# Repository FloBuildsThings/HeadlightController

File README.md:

# HeadlightController
Prototype for controlling a Headlight

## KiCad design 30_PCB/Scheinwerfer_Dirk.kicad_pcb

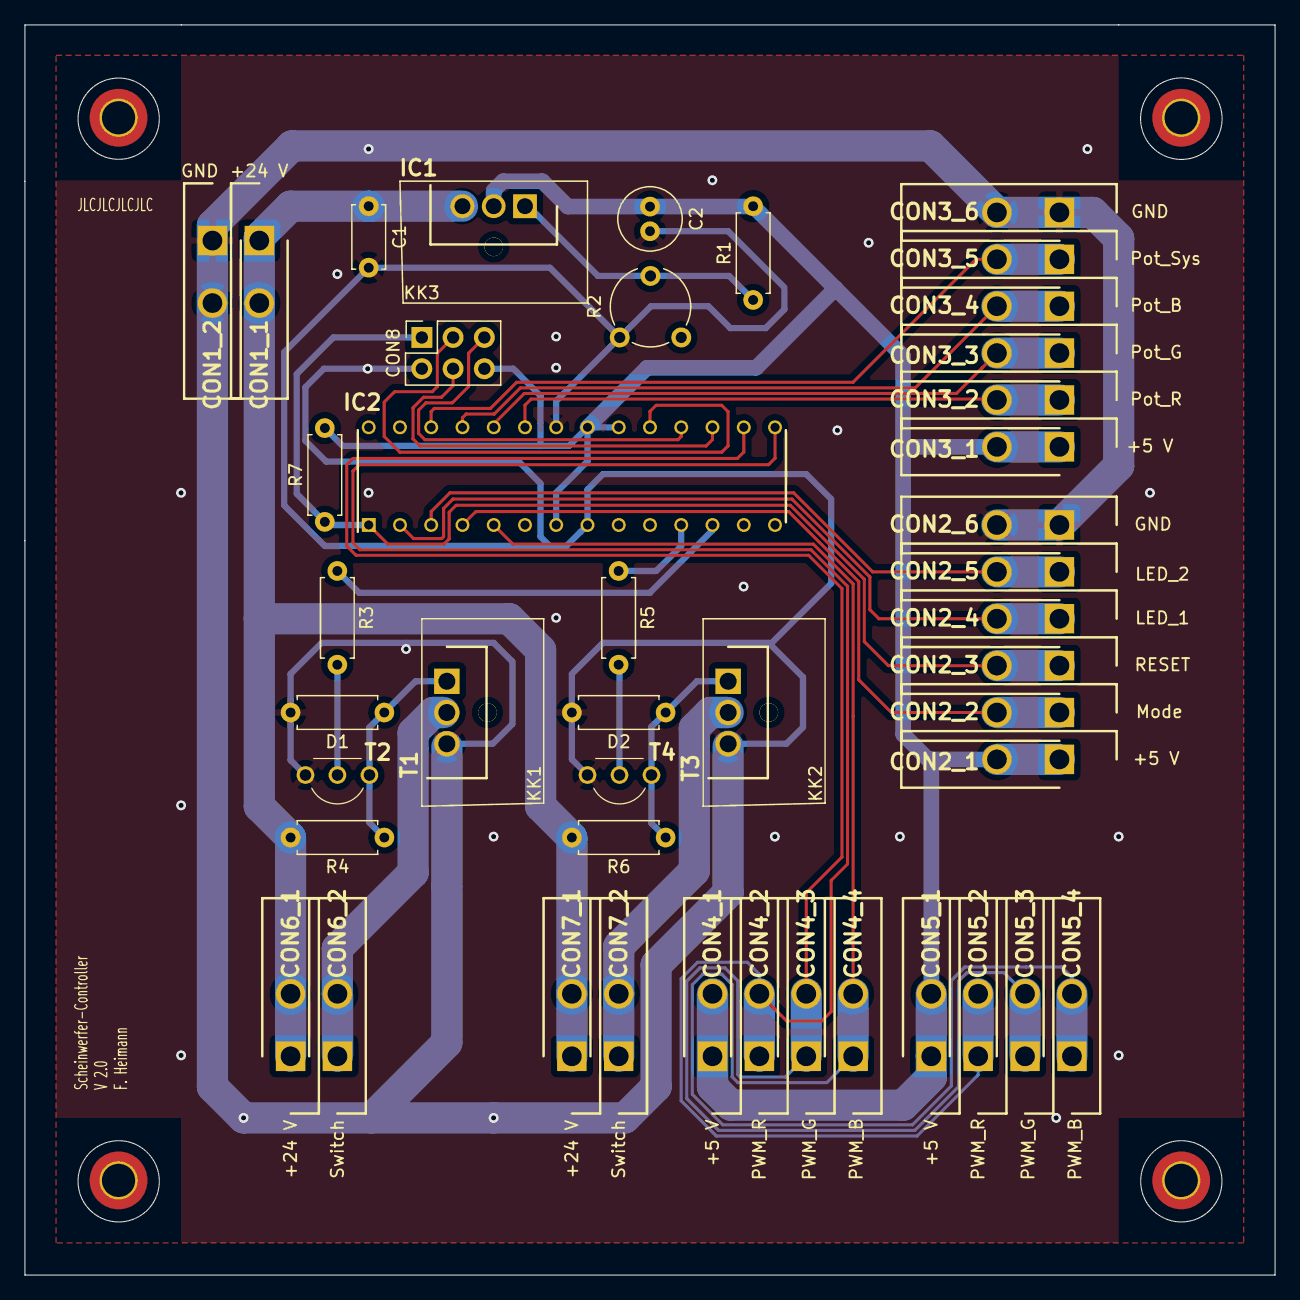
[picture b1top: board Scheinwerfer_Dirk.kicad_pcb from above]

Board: 2 copper layers, 101.6 x 101.6 mm, 47 parts (0 on the bottom side), 26 nets.

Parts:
C1: 0,1u; C_Disc_D5.0mm_W2.5mm_P5.00mm
C2: 1u; C_Radial_D5.0mm_H11.0mm_P2.00mm
CON1_1, CON1_2, CON2_1, CON2_2, CON2_3, CON2_4, CON2_5, CON2_6, CON3_1, CON3_2, CON3_3, CON3_4, CON3_5, CON3_6, CON4_1, CON4_2, CON4_3, CON4_4, CON5_1, CON5_2, CON5_3, CON5_4, CON6_1, CON6_2, CON7_1, CON7_2: 1704994; SHDR2W100P508X381_2X1_460X1750X1420P
CON8: ISP_DW_Connector
D1, D2: D_Zener; R_Axial_DIN0207_L6.3mm_D2.5mm_P7.62mm_Horizontal
IC1: LM317BTG; TO254P482X997X2018-3P
IC2: ATMEGA328P-PU; DIP794W53P254L3467H457Q28N
KK1, KK2, KK3: SK95-2M3; Heatsink_TO-220_L10_B15_H19.75
R1: 240; R_Axial_DIN0207_L6.3mm_D2.5mm_P7.62mm_Horizontal
R2: 3306F-1-504; Potentiometer_Piher_PT-6-V_Vertical
R3, R5: 120; R_Axial_DIN0207_L6.3mm_D2.5mm_P7.62mm_Horizontal
R4, R6: 10k; R_Axial_DIN0207_L6.3mm_D2.5mm_P7.62mm_Horizontal
R7: 4,7k; R_Axial_DIN0207_L6.3mm_D2.5mm_P7.62mm_Horizontal
T1, T3: IRFZ44N; TO254P483X1016X2223-3P
T2, T4: BC547ATA; TO-92__TO-226_

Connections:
+5V: C2.1, CON2_1.1, CON2_1.2, CON3_1.1, CON3_1.2, CON4_1.1, CON4_1.2, CON5_1.1, CON5_1.2, CON8.4, IC1.2, IC2.7, IC2.20, IC2.21, R1.2, R7.2
+24V: C1.1, CON1_1.1, CON1_1.2, CON6_1.1, CON6_1.2, CON7_1.1, CON7_1.2, IC1.3, R4.2, R6.2
/LED_1: CON2_4.1, CON2_4.2, IC2.2
/LED_2: CON2_5.1, CON2_5.2, IC2.3
/PWM_1: IC2.12, R3.1
/PWM_2: IC2.11, R5.1
/PWM_B: CON4_4.1, CON4_4.2, CON5_4.1, CON5_4.2, IC2.5
/PWM_G: CON4_3.1, CON4_3.2, CON5_3.1, CON5_3.2, IC2.16
/PWM_R: CON4_2.1, CON4_2.2, CON5_2.1, CON5_2.2, IC2.15
/Pot_B: CON3_4.1, CON3_4.2, IC2.25
/Pot_G: CON3_3.1, CON3_3.2, IC2.24
/Pot_R: CON3_2.1, CON3_2.2, IC2.23
/Pot_Sys: CON3_5.1, CON3_5.2, IC2.26
/SW_Mode: CON2_2.1, CON2_2.2, IC2.4
/uC_MISO: CON8.3, IC2.18
/uC_MOSI: CON8.5, IC2.17
/uC_RESET: CON2_3.1, CON2_3.2, CON8.1, IC2.1, R7.1
/uC_SCK: CON8.2, IC2.19
GND: C1.2, C2.2, CON1_2.1, CON1_2.2, CON2_6.1, CON2_6.2, CON3_6.1, CON3_6.2, CON8.6, D1.2, D2.2, IC2.8, IC2.22, R2.3, T1.3, T2.3, T3.3, T4.3
unnamed: CON6_2.1, CON6_2.2, T1.2
unnamed: CON7_2.1, CON7_2.2, T3.2
unnamed: D1.1, R4.1, T1.1, T2.1
unnamed: D2.1, R6.1, T3.1, T4.1
unnamed: IC1.1, R1.1, R2.2
unnamed: R3.2, T2.2
unnamed: R5.2, T4.2

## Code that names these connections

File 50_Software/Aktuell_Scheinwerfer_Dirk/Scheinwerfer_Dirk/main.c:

/*
 * Scheinwerfer_Dirk.c
 *
 * Created: 03.07.2020 08:35:33
 * Author : flo97
 */ 

/*
	Controller : ATMEGA328P U
	
	Pinout:
									   V
	ISP5	PCINT14/RESET		PC6	 1	28 PC5	ADC5/SCL/PCINT13	
	LED_1	PCINT16/RXD			PD0	 2	27 PC4	ADC4/SDA/PCINT12	
	LED_2	PCINT17/TXD			PD1	 3	26 PC3	ADC3/PCINT11		Poti Sys
	SW_MODE	PCINT18/INT0		PD2  4	25 PC2	ADC2/PCINT10		Poti B
	PWM B	PCINT19/OC2B/INT1	PD3  5	24 PC1	ADC1/PCINT9			Poti G
			PCINT20/XCK/T0		PD4  6	23 PC0	ADC0/PCINT8			Poti R
	5V							VCC  7	22 GND						0V
	0V							GND  8	21 AREF						5V
			PCINT6/XTAL1/TOSC1	PB6	 9	20 AVCC						5V
			PCINT7/XTAL2/TOSC2	PB7 10	19 PB5	SCK/PCINT5			ISP0
	FET1.2	PCINT21/OC0B/T1		PD5 11	18 PB4	MISO/PCINT4			ISP2
	FET1.1	PCINT22/OC0A/AIN0	PD6 12	17 PB3	MOSI/OC2A/PCINT3	ISP8
			PCINT23/AIN1		PC7 13	16 PB2	SS/OC1B/PCINT2		PWM G
			PCINT0/CLKO/ICP1	PB0 14	15 PB1	OC1A/PCINT1			PWM R
	
	ISP1 GND 
	ISP3 5V
*/

#define F_CPU 8000000UL

#define SweepSpeedMax 200 //RGB sweep time in µs
#define SweepSpeedMin 50000 //RGB sweep time in µs
#define SweepSpeedDefault 10000 //RGB sweep time in µs
#define SweepSpeedFast 200 //RGB sweep time in µs

#define LEDLimitMax 0x60
#define LEDLimitMin 0xEF
#define LEDSweepPrescaler 3

#define StartMode 0

//#define __DELAY_BACKWARD_COMPATIBLE__

#include <avr/io.h>
#include <util/delay.h>
#include <stdio.h>
#include <stdbool.h>

#include "init_Interrupts.h"
#include "init_Counter0_PWM.h"
#include "init_Counter1_PWM.h"
#include "init_Counter2_PWM.h"
#include "init_ADC.h"
#include "init_Test_LED.h"

//Variables
uint8_t lMode = StartMode;
uint16_t SweepSpeed = SweepSpeedDefault;

bool change_Mode = false;

uint8_t PotiR = 0;
uint8_t PotiG = 0;
uint8_t PotiB = 0;
uint8_t PotiSys = 0x20;

uint8_t ValueR = 0xFF;
uint8_t ValueG = 0xFF;
uint8_t ValueB = 0xFF;

uint8_t ValueLED = 0xFF;
uint8_t LEDSweepPrescaleCounter = 0x00;

uint8_t Int_Counter = 0;

bool RUp = 1;
bool GUp = 0;
bool BUp = 0;

bool RDown = 0;
bool GDown = 0;
bool BDown = 1;

bool LEDUp = 1;

void init()
{
	init_Interrupts();
	
	init_Counter0_PWM();
	init_Counter1_PWM();
	init_Counter2_PWM();
	
	init_ADC();
}

void testLoop()
{
	OCR0A = 0xFF; //LED Bot 0xFF=off 0x00=on
	OCR0B = 0xFF; //LED Top 0xFF=off 0x00=on
	OCR1A = 0XFF; //R 0xFF=off 0x00=on
	OCR1B = 0xFF; //G 0xFF=off 0x00=on
	OCR2B = 0xFF; //B 0xFF=off 0x00=on
}

void readPotis()
{
	PotiR = readADC(0);
	PotiG = readADC(1);
	PotiB = readADC(2);
	PotiSys = readADC(3);
	
}

void RGBSweep()
{
	if(RUp)
	{
		ValueR--;
		if(ValueR<=0)
		{
			ValueR = 0;
			GUp = true;
			RUp = false;
			BDown = true;
		}
	}
	
	if(GUp)
	{
		ValueG--;
		if(ValueG<=0)
		{
			ValueG = 0;
			BUp = true;
			GUp = false;
			RDown = true;
		}
	}
	
	if(BUp)
	{
		ValueB--;
		if(ValueB<=0)
		{
			ValueB = 0;
			RUp = true;
			BUp = false;
			GDown = true;
		}
	}
	
	if(RDown)
	{
		ValueR++;
		if(ValueR>=255)
		{
			ValueR=255;
			RDown = false;
			GDown = true;
		}
	}
	if(GDown)
	{
		ValueG++;
		if(ValueG>=255)
		{
			ValueG=255;
			GDown = false;
			BDown = true;
		}
	}
	
	if(BDown)
	{
		ValueB++;
		if(ValueB>=255)
		{
			ValueB=255;
			BDown = false;
			RDown = true;
		}
	}
	
	
	OCR1A = ValueR;
	OCR1B = ValueG;
	OCR2B = ValueB;
}

void LEDSweep()
{
	if(LEDSweepPrescaleCounter >= LEDSweepPrescaler)
	{
		LEDSweepPrescaleCounter = 0;
		if(LEDUp)
		{
			ValueLED--;
			if(ValueLED <= LEDLimitMax)
			{
				ValueLED = LEDLimitMax;
				LEDUp = false;
			}
		}
		else
		{
			ValueLED++;
			if(ValueLED >= LEDLimitMin)
			{
				ValueLED = LEDLimitMin;
				LEDUp = true;
			}
		}
		OCR0A = ValueLED;
		OCR0B = OCR0A;
	}
	else
	{
		LEDSweepPrescaleCounter++;
	}
}

int main(void)
{
	//Init
	init();
	sei();
	
	testLoop();
	

	
	//Code   
	while (1)
	{   
		if(lMode == 0)
		{
			LEDSweep();
			RGBSweep();
			_delay_us(SweepSpeedDefault);
		}
		else if(lMode == 1)
		{
			LEDSweep();
			RGBSweep();
			_delay_us(SweepSpeedFast);
		}
		else if(lMode == 2)
		{
			OCR0A = PotiSys;
			OCR0B = OCR0A;
			
			OCR1A = PotiR;
			OCR1B = PotiG;
			OCR2B = PotiB;
			_delay_us(SweepSpeedDefault);
		}
		else if(lMode ==  3)
		{
			OCR0A = PotiSys;
			OCR0B = OCR0A;
			
			RGBSweep();
			_delay_us(SweepSpeedDefault);
		}
		else
		{
			lMode = 0;
		}
		
		if(change_Mode == true)
		{
			lMode++;
			if(lMode >= 4)
			{
				lMode = 0;
			}
			
			change_Mode = false;
			Int_Counter = 0;
		}
		readPotis();		
	}		
}

ISR (INT0_vect)
{
	change_Mode = true;
	Int_Counter++;
}
